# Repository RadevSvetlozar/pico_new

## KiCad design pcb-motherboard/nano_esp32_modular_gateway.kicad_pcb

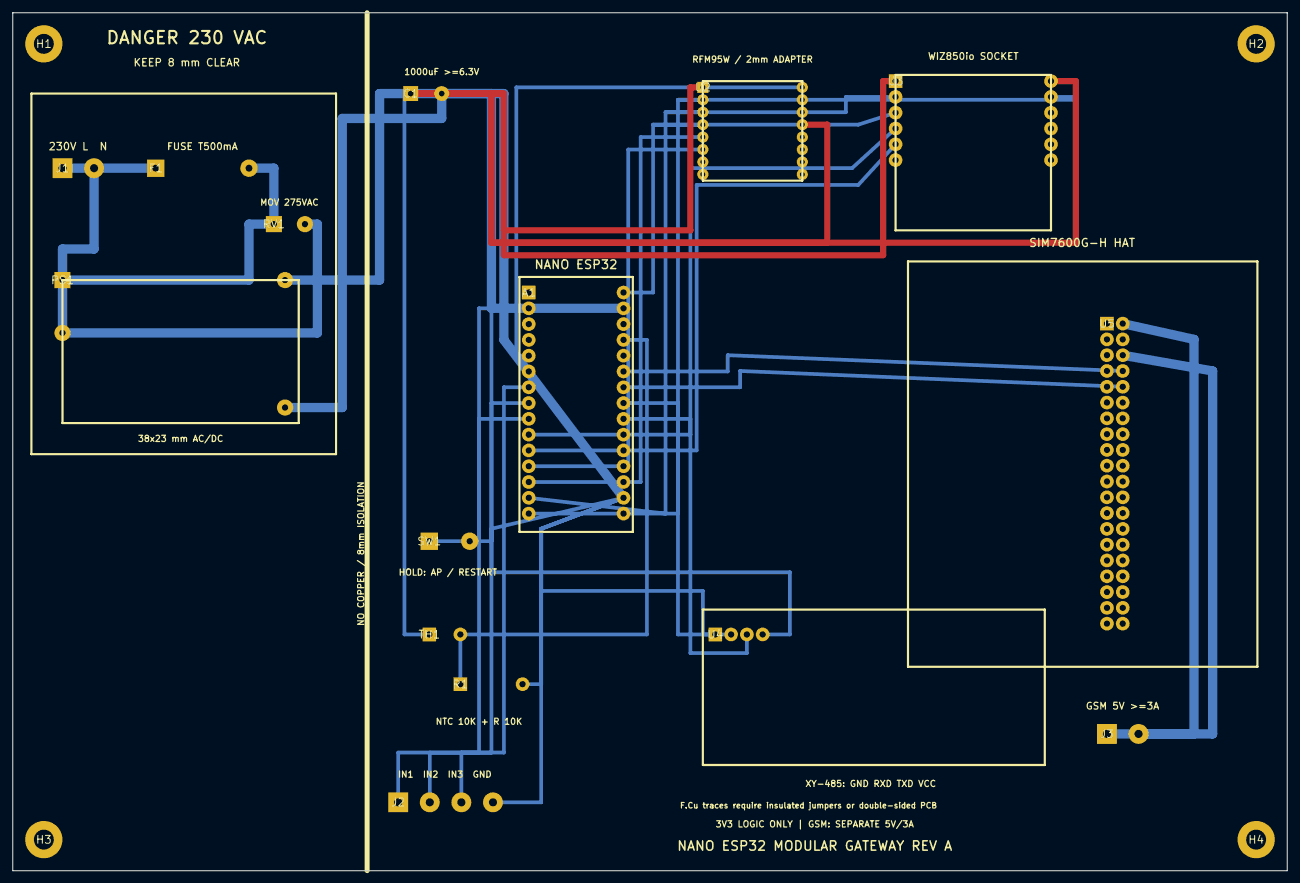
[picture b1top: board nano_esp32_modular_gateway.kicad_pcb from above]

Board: 2 copper layers, 205.0 x 138.0 mm, 19 parts (0 on the bottom side), 24 nets.

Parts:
A1: Arduino_Nano_ESP32_socket
C1: 1000uF_6V3
F1: FUSE_T500mA
H1, H2, H3, H4: M3
J1: AC_IN_5.08
J2: LOCAL_INPUTS_5.08
J3: GSM_5V_IN_5.08
PS1: ACDC_38x23_3V3
R1: 10K
RV1: MOV_275VAC
SW1: AP_CONFIG_BUTTON
TH1: NTC_10K
U2: RFM95W_16x16_P2.0
U3: WIZ850io_socket
U4: XY-485_1x4
U5: SIM7600G-H_HAT_2x20

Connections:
+3V3: A1.29, C1.1, PS1.4, TH1.1, U2.13, U3.12, U4.4
+5V_GSM: J3.1, U5.2, U5.4
A0: A1.27, R1.1, TH1.2
A2_RX: A1.25, U5.8
A3_TX: A1.24, U5.10
A4_TX: A1.23, U4.2
A5_RX: A1.22, U4.3
AC_L: F1.1, J1.1
AC_L_FUSED: F1.2, PS1.1, RV1.1
AC_N: J1.2, PS1.2, RV1.2
D0_RX: A1.2, SW1.1
D2: A1.5, U2.16
D4: A1.7, J2.1
D5: A1.8, J2.2
D6: A1.9, J2.3
D7: A1.10, U3.4
D8: A1.11, U3.5
D9: A1.12, U2.6
D10: A1.13, U2.5
D11_MOSI: A1.14, U2.3, U3.2
D12_MISO: A1.15, U2.2, U3.11
D13_SCK: A1.30, U2.4, U3.3
GND: A1.4, A1.17, C1.2, J2.4, J3.2, PS1.3, R1.2, SW1.2, U2.1, U2.8, U2.10, U3.1, U3.7, U4.1, U5.6, U5.9, U5.14, U5.20, U5.25, U5.30, U5.34, U5.39
RESET: A1.3, A1.18, U3.6

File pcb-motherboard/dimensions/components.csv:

ref,value,origin_x_mm,origin_y_mm,pads,pad_span_xy_mm,pitch_x_mm,pitch_y_mm,pad_size_mm,drill_mm,drawn_outline_mm
A1,Arduino_Nano_ESP32_socket,83.0,45.0,30,15.24 × 35.56,15.24,2.54,2.2 × 2.2,1,18.24 × 41
C1,1000uF_6V3,64.0,13.0,2,5 × 0,5,—,2.4 × 2.4,0.9,Не е зададен
F1,FUSE_T500mA,23.0,25.0,2,15 × 0,15,—,2.8 × 2.8,1.1,Не е зададен
H1,M3,5.0,5.0,1,0 × 0,—,—,6 × 6,3.2,Не е зададен
H2,M3,200.0,5.0,1,0 × 0,—,—,6 × 6,3.2,Не е зададен
H3,M3,5.0,133.0,1,0 × 0,—,—,6 × 6,3.2,Не е зададен
H4,M3,200.0,133.0,1,0 × 0,—,—,6 × 6,3.2,Не е зададен
J1,AC_IN_5.08,8.0,25.0,2,5.08 × 0,5.08,—,3.2 × 3.2,1.3,Не е зададен
J2,LOCAL_INPUTS_5.08,62.0,127.0,4,15.24 × 0,5.08,—,3.2 × 3.2,1.3,Не е зададен
J3,GSM_5V_IN_5.08,176.0,116.0,2,5.08 × 0,5.08,—,3.2 × 3.2,1.3,Не е зададен
PS1,ACDC_38x23_3V3,8.0,43.0,4,35.8 × 20.5,35.8,"8.5, 12",2.6 × 2.6,1,38 × 23
R1,10K,72.0,108.0,2,10 × 0,10,—,2.2 × 2.2,1,Не е зададен
RV1,MOV_275VAC,42.0,34.0,2,5 × 0,5,—,2.6 × 2.6,1,Не е зададен
SW1,AP_CONFIG_BUTTON,67.0,85.0,2,6.5 × 0,6.5,—,2.8 × 2.8,1,Не е зададен
TH1,NTC_10K,67.0,100.0,2,5 × 0,5,—,2.2 × 2.2,1,Не е зададен
U2,RFM95W_16x16_P2.0,111.0,12.0,16,16 × 14,16,2,1.8 × 1.8,0.8,16 × 16
U3,WIZ850io_socket,142.0,11.0,12,25 × 12.7,25,2.54,2.2 × 2.2,1,25 × 25
U4,XY-485_1x4,113.0,100.0,4,7.62 × 0,2.54,—,2.2 × 2.2,1,55 × 25
U5,SIM7600G-H_HAT_2x20,176.0,50.0,40,2.54 × 48.26,2.54,2.54,2.2 × 2.2,1,56.2 × 65.2

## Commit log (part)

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2025-07-25 init commit
2025-07-25 version 1.1
2025-07-25 1.1.0
2025-07-26 rtrrt
2025-07-26 yyyy
2025-09-15 dsad
2025-09-26 dsda
2025-09-26 ddddd
2026-04-08 added copy of request
2026-04-08 added reset button for factory reset
2026-04-10 added fallback functions
